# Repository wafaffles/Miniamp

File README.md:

# Miniamp
A portable, battery powered Hi-Fi DAC and headphone amplifier.

## Shortcuts
- [Features](#features)
- [What is it?](#what-is-it)
- [Resources](#resources)
- [Assembly](#assembly)
- [Bill Of Materials](#bill-of-materials)
- [Photos](#photos)

## Miniamp Zine

## Features

- Independent USB-C Ports
  - Top Mounted Data Only USB-C
  - Side Mounted Power Only USB-C
- Variable Size Audio Outputs
  - 1/4"
  - 3.5mm
- 5 Physical Media Control Buttons
- Toggleable Power Switch
- 2 Integrated 18650 Batteries
  - Avoids Discharging Connected Device (e.g., Mobile Phone, Laptop)
- Small Form Factor

## What is it?

Miniamp is a portable, battery powered DAC and headphone amp designed for phones, portable devices, or for desk deployments. The Miniamp features a Hifi DAC chip capable of producing 24bit 44.1kHz outputs at 2.1Vrms, with adequite power for majority of headphones. It utilizes a Silicon Labs CP2615-A02-GM USB to I2S chip, a Cirrus Logic WM8524CGEDT DAC, and an Analog Devices MAX97220AETE+T headphone amplifier. It also has a battery charging and protection circuit to handle charing, protection, and output regulation to the ICs using 2 18650 batteries in a 1s2p configuration. This setup removes power draw from the data streaming device and offloads it to the batteries, with a passthrough power circuit to power all devices externally with a long battery life.

I created this to have an easy device to bring around with me at school so I can use my wired headphones and control them without the need to open my phone for controls or worry about my phone dying which was really nice. It should work well and do exactly that since I love the apple dongle, but its just super small, feels like its gonna break, and just kinda basic without any controls.
 
## Resources

CAD Link: https://cad.onshape.com/documents/a14a9a55c78bf32f82e1c97a/w/0351478092a46614c60a771f/e/1fa4c67b30b50298fb86e419?renderMode=0&uiState=6a336e0a197a1dd98d81aa96

CAD Files: [HERE](/3DModels)

ECAD Files: [HERE](/Models/ECADModels_Production/)

Production Files: [HERE](/Resources/)

## Assembly

You will need:
- PCB (PCBA with ICs attached if you do not have a way to solder smd parts without legs, the assumed method of this assembly guide)
- Rest of ICS needed
- Required Heatset Inserts
- All printed parts
- Soldering iron
- Solder
- Matching screwdriver to screw set (allen key in provided kit)
- Small pair of tweasers

1. Gather all resources, print all case parts, and have a clean open workspace
2. Carefully solder all components not installed with PCBA according to the schematics and ECAD files (most resistors, caps, and all THT parts)
3. With the PCB assembled now, to start assembling the case you want to heat your soldering iron to about 225°C and carefully insert the M3 heatset inserts into the standoffs on the top case part.
4. Now that both the case is assembled and ready, and the PCB is ready, test the PCB outside of its case to ensure it will work without issue. If there is an error, seek help or investigate to make sure all components are placed correctly.
5. Insert the PCB into the top case, slide on the TPU band, and screw in the bottom case using the 4 M3 bolts
6. Enjoy!

## Bill Of Materials

BOM: [HERE](https://docs.google.com/spreadsheets/d/1Rq9yz0U521aMRGwPaQNTlH2bsf_DakTQIQjvENSfLP8/edit?usp=sharing)

PCBA BOM: [HERE](https://docs.google.com/spreadsheets/d/17-cePCVTrSii_cqeCaBxXgTqAQEytrTk/edit?usp=sharing&ouid=108713575531525219545&rtpof=true&sd=true)

Both can be found in files, normal BOM [here](/Resources/) and the PCBA BOM [here](/Models/ECADModels_Production/)

## Photos

Miniamp Main PCB Schematic

Miniamp Power PCB Schematic

Miniamp Case Front

Miniamp Case Back

Miniamp Case Inside

PCB All Layers

PCB F.Cu Layer

PCB In1.Cu Layer

PCB In2.Cu Layer

PCB In3.Cu Layer

PCB In4.Cu Layer

PCB B.Cu Layer

Top of PCB

Bottom of PCB

Render of PCB

## Credits

This project uses:

- [KiCad](https://www.kicad.org/)
- [Figma](https://www.figma.com/)
- [Hack Club Fallout](https://fallout.hackclub.com/path)

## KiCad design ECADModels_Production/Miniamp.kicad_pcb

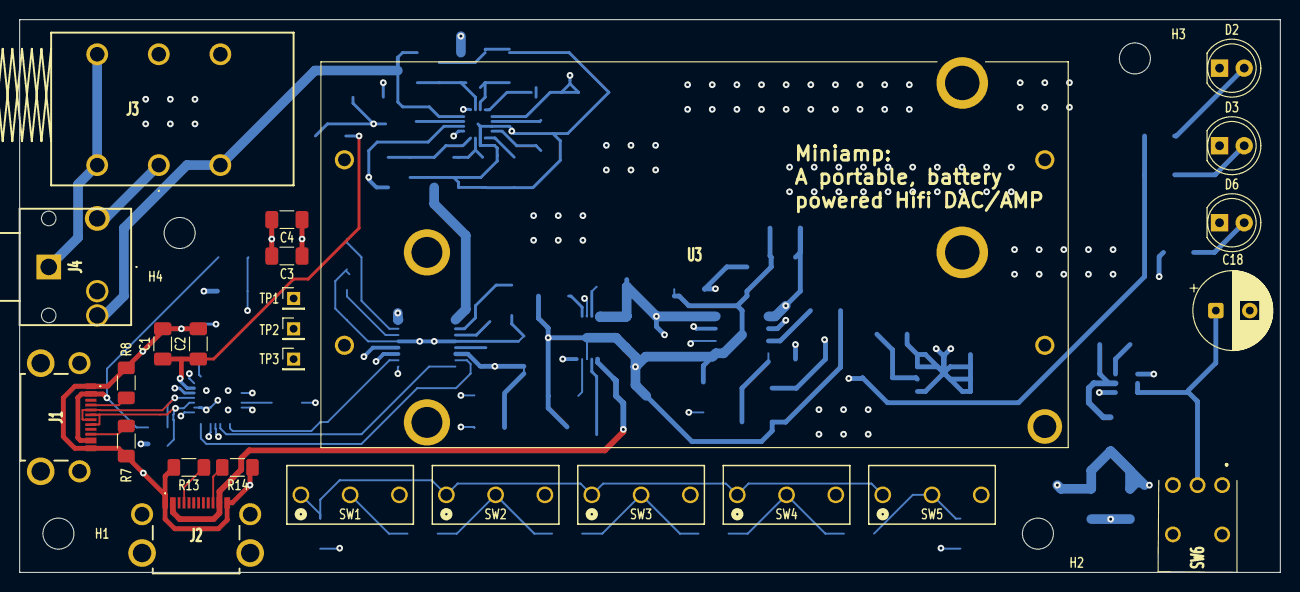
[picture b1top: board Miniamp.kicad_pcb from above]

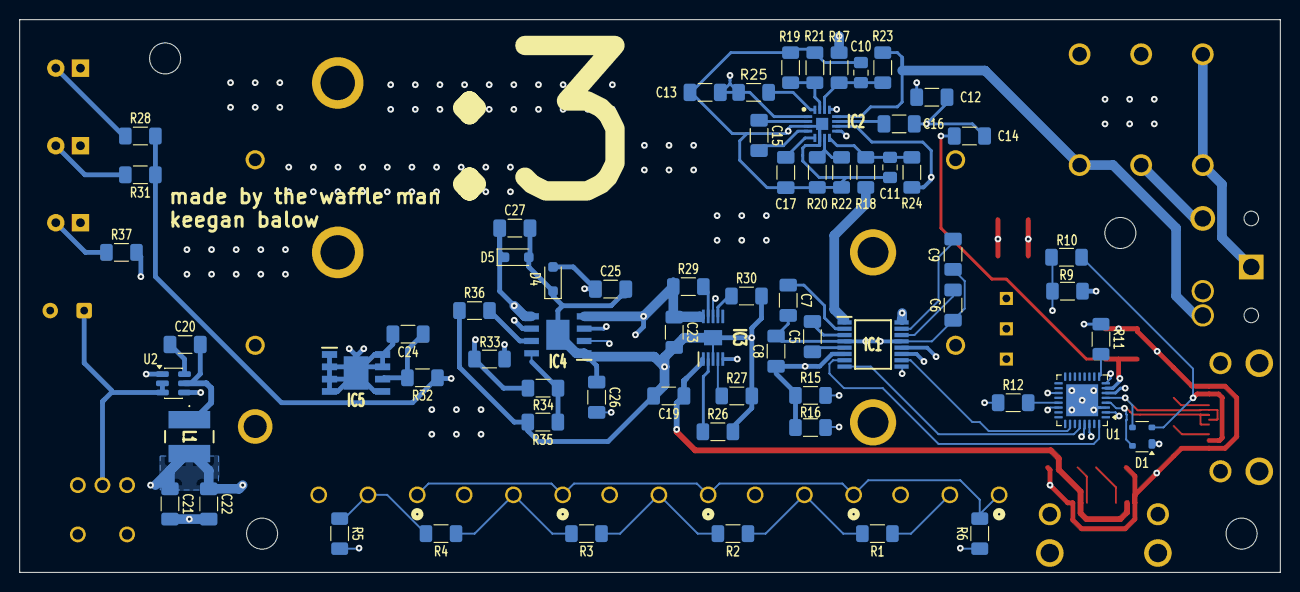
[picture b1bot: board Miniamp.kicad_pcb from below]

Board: 6 copper layers, 130.0 x 57.0 mm, 96 parts (66 on the bottom side), 67 nets.

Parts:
C1, C3, C5, C7, C12, C13, C14, C15, C17, C19, C23: 1uF; C_1206_3216Metric_Pad1.33x1.80mm_HandSolder
C2, C4, C16, C20, C24, C25, C27: .1uF; C_1206_3216Metric_Pad1.33x1.80mm_HandSolder
C6: 2.2uF; C_1206_3216Metric_Pad1.33x1.80mm_HandSolder
C8, C9: 4.7uF; C_1206_3216Metric_Pad1.33x1.80mm_HandSolder
C10, C11: 2.7nF; C_0805_2012Metric_Pad1.18x1.45mm_HandSolder
C18: 10uF; CP_Radial_D8.0mm_P3.50mm
C21, C22: 22uF; C_1206_3216Metric_Pad1.33x1.80mm_HandSolder
C26: 2.2nf; C_1206_3216Metric_Pad1.33x1.80mm_HandSolder
D1: SP0503BAHT; SOT-143
D2: GRN; LED_D5.0mm
D3: RED; LED_D5.0mm
D4, D5: D,Schottky,IEC; D_SOD-323_HandSoldering
D6: 2V YLW; LED_D5.0mm
H1, H2, H3, H4: M3 Mounting Hole; MountingHole_3.2mm_M3
IC1: WM8524CGEDT; SOP65P640X120-16N
IC2: MAX97220AETE+T; QFN50P300X300X80-17N
IC3: BQ24093DGQR; SOP50P490X110-11N
IC4: TPS259631DDAR; SOIC127P600X170-9N
IC5: XB8089D; SOIC127P605X175-9N
J1, J2: USB_C_Receptacle_USB2.0_16P; UJ20CHGMSMT2BP16TR
J3: ACJS-MHOM; ACJSMHOM
J4: SJ1-3554NG; SJ13554NG
L1: 4.7uH; SDCH1V50404R7MR
R1, R2: 15k 1%; R_1206_3216Metric_Pad1.30x1.75mm_HandSolder
R3, R4: 10k 1%; R_1206_3216Metric_Pad1.30x1.75mm_HandSolder
R5: 8.25k 1%; R_1206_3216Metric_Pad1.30x1.75mm_HandSolder
R6: 100k 1%; R_1206_3216Metric_Pad1.30x1.75mm_HandSolder
R7, R8, R13, R14: 5.1k; R_1206_3216Metric_Pad1.30x1.75mm_HandSolder
R9: 24k; R_1206_3216Metric_Pad1.30x1.75mm_HandSolder
R10: 47k; R_1206_3216Metric_Pad1.30x1.75mm_HandSolder
R11, R12: 4.7k; R_1206_3216Metric_Pad1.30x1.75mm_HandSolder
R15, R16, R19, R20, R21, R22, R23, R24, R25, R29, R30: 10k; R_1206_3216Metric_Pad1.30x1.75mm_HandSolder
R17, R18: 560; R_1206_3216Metric_Pad1.30x1.75mm_HandSolder
R26, R32: 1k; R_1206_3216Metric_Pad1.30x1.75mm_HandSolder
R27: 2k; R_1206_3216Metric_Pad1.30x1.75mm_HandSolder
R28, R31: 1.5k; R_1206_3216Metric_Pad1.30x1.75mm_HandSolder
R33: 590k 1%; R_1206_3216Metric_Pad1.30x1.75mm_HandSolder
R34: 124k 1%; R_1206_3216Metric_Pad1.30x1.75mm_HandSolder
R35: 274k 1%; R_1206_3216Metric_Pad1.30x1.75mm_HandSolder
R36: 909 1%; R_1206_3216Metric_Pad1.30x1.75mm_HandSolder
R37: 300; R_1206_3216Metric_Pad1.30x1.75mm_HandSolder
SW1, SW2, SW3, SW4, SW5: SW_SPST; ZMA00A150L04RC
SW6: SW_PWR; 400AWMSP1R1BLKM6QE
TP1: GPIO.10; PinHeader_1x01_P2.00mm_Vertical
TP2: I2C_SCL; PinHeader_1x01_P2.00mm_Vertical
TP3: I2C_SDA; PinHeader_1x01_P2.00mm_Vertical
U1: CP2615-xx-xM; QFN-32-1EP_5x5mm_P0.5mm_EP3.3x3.3mm
U2: AP63205WU; TSOT-23-6
U3: 2x 18650 Battery; 1049

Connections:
/5V_FROM_BATT: C1.1, C2.1, C12.2, C13.1, C14.2, C21.1, C22.1, IC2.1 (PVDD), IC2.9 (SVDD2), IC2.13 (SVDD), L1.2, R25.1, U1.7 (REGIN), U2.1 (FB)
/AOUTL: IC1.16 (LINEVOUTR), R17.1
/AOUTR: IC1.1 (LINEVOUTL), R18.1
/Battery Charger & Power/CHRG_OUT: C23.1, C25.1, D4.2 (A+), IC3.10 (OUT), IC4.4 (IN), R28.2, R29.1, R31.1, R32.1, R33.1, U3.6, U3.7
/Battery Charger & Power/PROT_OUT: C18.1, SW6.2 (B), U2.2 (EN), U2.3 (IN)
/D_IN_+: D1.4 (K), J1.A6 (D+), J1.B6 (D+), U1.4 (D+)
/D_IN_-: D1.3 (K), J1.A7 (D-), J1.B7 (D-), U1.5 (D-)
/GPIO BUTTONS: R6.2, SW1.1 (A), SW2.1 (A), SW3.1 (A), SW4.1 (A), SW5.1 (A), U1.19 (GPIO.9/BUTTONS)
/L_PHONES: IC2.12 (OUTL), J3.T1, J4.2 (TIP), R23.2
/R_PHONES: IC2.10 (OUTR), J3.R1, J4.3 (RING), R24.2
GND: C1.2, C2.2, C3.2, C4.2, C6.1, C7.2, C8.2, C9.2, C10.2, C11.2, C12.1, C13.2, C14.1, C16.2, C17.2, C18.2, C19.2, C21.2, C22.2, C23.2, C24.2, C25.2, C26.1, C27.2, D1.1 (A), D4.1 (K-), D5.2 (A+), IC1.4 (LINEGND), IC1.13 (AGND), IC2.3 (PGND), IC2.6 (SGND), IC2.17 (EP), IC3.3 (VSS), IC3.11 (EP), IC4.1 (GND_1), IC4.9 (GND_2), IC5.1 (VM_1), IC5.2 (VM_2), IC5.3 (VM_3), IC5.4 (VM_4), IC5.5 (GND_1), IC5.7 (GND_2), IC5.8 (GND_3), IC5.9 (EPAD), J1.A1 (GND), J1.B1 (GND), J2.A1 (GND), J2.B1 (GND), J3.S1, J3.S2, J4.1 (SLEEVE), R5.2, R7.2, R8.2, R10.2, R13.2, R14.2, R19.1, R20.1, R21.2, R22.1, R26.2, R27.2, R30.2, R35.2, R36.1, U1.3 (GND), U1.33 (GND), U2.4 (GND), U3.8, U3.9
unnamed: D1.2 (K), J1.A4 (VBUS), J1.B4 (VBUS), R9.1
unnamed: D2.2 (A), R28.1
unnamed: D2.1 (K), IC3.5 (~PG)
unnamed: D3.2 (A), R31.2
unnamed: D3.1 (K), IC3.8 (~CHG)
unnamed: C27.1, D5.1 (K-), IC4.5 (OUT), R37.2, SW6.1 (A)
unnamed: D6.2 (A), R37.1
unnamed: D6.1 (K), IC4.6 (~FLT)
unnamed: IC1.12 (AIFMODE), R16.2
unnamed: C9.1, IC1.15 (AVDD)
unnamed: IC1.9 (BCLK), U1.2 (I2S_SCLK)
unnamed: C5.2, IC1.5 (CPCA)
unnamed: C5.1, IC1.3 (CPCB)
unnamed: C7.1, IC1.2 (CPVOUTN)
unnamed: IC1.7 (DACDAT), U1.32 (I2S_SDOUT)
unnamed: IC1.8 (LRCLK), U1.28 (I2S_LRCLK)
unnamed: IC1.10 (MCLK), U1.26 (I2S_MCLK)
unnamed: C6.2, IC1.14 (VMID)
unnamed: IC1.11 (~MUTE), R15.2
unnamed: C16.1, IC2.11 (BIAS)
unnamed: C15.2, IC2.4 (C1N)
unnamed: C15.1, IC2.2 (C1P)
unnamed: IC2.15 (INL+), R19.2, R21.1
unnamed: C10.1, IC2.14 (INL-), R17.2, R23.1
unnamed: IC2.7 (INR+), R20.2, R22.2
unnamed: C11.1, IC2.8 (INR-), R18.2, R24.1
unnamed: C17.1, IC2.5 (PVSS)
unnamed: IC2.16 (~SHDN), R25.2
unnamed: IC3.7 (ISET2), R30.1
unnamed: IC3.2 (ISET), R26.1
unnamed: IC3.4 (PRETERM), R27.1
unnamed: IC3.9 (TS), R29.2
unnamed: C26.2, IC4.2 (DVDT)
unnamed: IC4.3 (EN/UVLO), R33.2, R34.1
unnamed: IC4.7 (ILM), R36.2
unnamed: IC4.8 (OVLO/OVCSEL), R34.2, R35.1
unnamed: C24.1, IC5.6 (VDD), R32.2
unnamed: J1.A5 (CC1), R8.1
unnamed: J1.B5 (CC2), R7.1
unnamed: J2.A5 (CC1), R13.1
unnamed: J2.B5 (CC2), R14.1
unnamed: R1.1, SW1.2 (B)
unnamed: R1.2, R2.1, SW2.2 (B)
unnamed: R2.2, R3.1, SW3.2 (B)
unnamed: R3.2, R4.1, SW4.2 (B)
unnamed: R4.2, R5.1, SW5.2 (B)
unnamed: TP1.1 (1_1), U1.22 (GPIO.10/~RESETOUT)
unnamed: TP2.1 (1_1), U1.29 (I2C_SCL)
unnamed: TP3.1 (1_1), U1.30 (I2C_SDA)
unnamed: R9.2, R10.1, U1.8 (VBUS)
unnamed: R12.2, U1.21 (~CFGMODE)
unnamed: R11.2, U1.9 (~RST)
unnamed: C20.1, U2.6 (BST)
unnamed: C20.2, L1.1, U2.5 (SW)
VBUS: C19.1, IC3.1 (IN), J2.A4 (VBUS), J2.B4 (VBUS)
VDD: C3.1, C4.1, C8.1, IC1.6 (LINEVDD), R6.1, R11.1, R12.1, R15.1, R16.1, U1.6 (VDD)

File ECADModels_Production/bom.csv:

Designator,Footprint,Quantity,Value,LCSC Part #
"C1, C12, C13, C14, C15, C17, C19, C23, C3, C5, C7",1206,11,1uF,C318771
"C10, C11",0805,2,2.7nF,
"C16, C2, C20, C24, C25, C27, C4",1206,7,.1uF,
C18,CP_Radial_D8.0mm_P3.50mm,1,10uF,C2168319
"C21, C22",1206,2,22uF,
C26,1206,1,2.2nf,
C6,1206,1,2.2uF,
"C8, C9",1206,2,4.7uF,
D1,SOT-143,1,SP0503BAHT,C7074
D2,LED_D5.0mm,1,GRN,
D3,LED_D5.0mm,1,RED,
"D4, D5",D_SOD-323_HandSoldering,2,"D,Schottky,IEC",C2762697
D6,LED_D5.0mm,1,2V YLW,
IC1,SOP65P640X120-16N,1,WM8524CGEDT,C146242
IC2,QFN50P300X300X80-17N,1,MAX97220AETE+T,C2682711
IC3,SOP50P490X110-11N,1,BQ24093DGQR,C2871988
IC4,SOIC127P600X170-9N,1,TPS259631DDAR,C2155778
IC5,SOIC127P605X175-9N,1,XB8089D,C79928
"J1, J2",UJ20CHGMSMT2BP16TR,2,USB_C_Receptacle_USB2.0_16P,
J3,ACJSMHOM,1,ACJS-MHOM,
J4,SJ13554NG,1,SJ1-3554NG,
L1,SDCH1V50404R7MR,1,4.7uH,
"R1, R2",1206,2,15k 1%,
R10,1206,1,47k,
"R11, R12",1206,2,4.7k,
"R13, R14, R7, R8",1206,4,5.1k,
"R15, R16, R19, R20, R21, R22, R23, R24, R25, R29, R30",1206,11,10k,C871997
"R17, R18",1206,2,560,C872823
"R26, R32",1206,2,1k,
R27,1206,1,2k,
"R28, R31",1206,2,1.5k,
"R3, R4",1206,2,10k 1%,
R33,1206,1,590k 1%,
R34,1206,1,124k 1%,
R35,1206,1,274k 1%,
R36,1206,1,909 1%,
R37,1206,1,300,
R5,1206,1,8.25k 1%,
R6,1206,1,100k 1%,
R9,1206,1,24k,
"SW1, SW2, SW3, SW4, SW5",ZMA00A150L04RC,5,SW_SPST,
SW6,400AWMSP1R1BLKM6QE,1,SW_PWR,
TP1,PinHeader_1x01_P2.00mm_Vertical,1,GPIO.10,
TP2,PinHeader_1x01_P2.00mm_Vertical,1,I2C_SCL,
TP3,PinHeader_1x01_P2.00mm_Vertical,1,I2C_SDA,
U1,QFN-32-1EP_5x5mm_P0.5mm_EP3.3x3.3mm,1,CP2615-xx-xM,C1521596
U2,TSOT-23-6,1,AP63205WU,C2071056
U3,1049,1,2x 18650 Battery,

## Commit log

2026-06-16 File Change/Setup
2026-06-17 Cad+Rearrange
2026-06-17 Updated BOM
2026-06-17 Updated Readme assembly
2026-06-18 cad refresh/almost done readme/new images and renders
2026-06-18 render and zine v1
2026-06-19 Fianlized all the stuff
